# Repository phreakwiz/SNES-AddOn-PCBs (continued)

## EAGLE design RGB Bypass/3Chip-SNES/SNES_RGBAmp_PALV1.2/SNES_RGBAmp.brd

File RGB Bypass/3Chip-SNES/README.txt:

SNES_RGBAmp: for PAL 3Chip-SNES boards (SNSP-CPU-01/02)  
  
-----------------------------------------------------------------------------------  
  
Installation:  
  
  - remove R8, R9, R13, R14, R18, R19 and Q4, Q6, Q8 from the SNES mainboard  
  - solder the three 1.87kOhm resistors to R8, R13 and R18  
  - solder the three 750Ohm resistors to R9, R14 and R19  
  - solder the directly beneath the MultiAV  
  - connect pad 'R' with the pad where the base of Q4 was  
  - connect pad 'G' with the pad where the base of Q6 was  
  - connect pad 'B' with the pad where the base of Q8 was  
  
While modding some components on the PCB may vary depending on your RGB cable you want to use.  
See the notes related to the components!    
  
-----------------------------------------------------------------------------------  
  
Components needed:  
  
1. Parts for the PCB:  
 - 1x THS7314 SOIC-8 package   
  
 - 1x 22uF/6.3V tantalum capacitor type-C package  
 - 1x 100nF/50V ceramic capacitor 0805 package  
  
 - 3x 82nF/50V ceramic capacitor 0805 package  
 - 3x 3.6MOhm resistor 0805 package (0.125W, 1% tolerance should be fine)   
  
2.a) Additional parts for the PCB for using NTSC-cable schematic [1]:  
 - 3x 75Ohm resistor 0805 package (0.125W, 1% tolerance should be fine)  
  
2.b) Additional parts for using PAL-cable schematic [1]:  
 - 3x 39Ohm resistor 0805 package (0.125W, 1% tolerance should be fine) [2]  
 - 3x 330uF/6.3V tantalum capacitor type-D package  
  
2.c) Additional parts for a cable with direct wiring RGB [1]:  
 - 3x 75Ohm resistor 0805 package (0.125W, 1% tolerance should be fine)  
 - 3x 330uF/6.3V tantalum capacitor type-D package  
  
3. Parts for the SNES mainboard:  
 - 3x 750Ohm resistor 0805 package (0.125W, 1% tolerance should be fine)  
 - 3x 1.87kOhm resistor 0805 package (0.125W, 1% tolerance should be fine)   
  
-----------------------------------------------------------------------------------  
  
Notes  
  
[1]  
Just pic one (!) and do not buy all parts. If you use NTSC-cable schematic you have to short the three jumpers on the PCB.  
  
[2]  
You could also use 6x 75Ohm resistor (0805 package (0.125W, 1% tolerance should be fine)) and stack two of them on each pad pair.

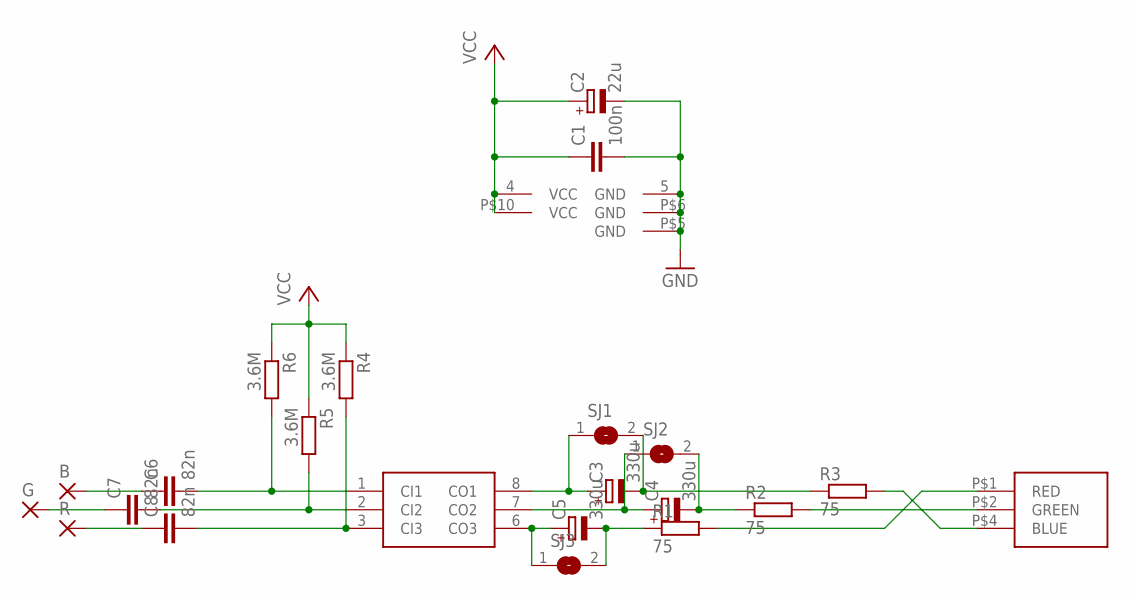
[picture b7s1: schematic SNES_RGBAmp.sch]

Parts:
B: SMD2; SMD1,27-2,54
C1: 100n; Z0805
C2: 22u; SMC_C
C3, C4, C5: 330u; SMC_D
C6, C7, C8: 82n; Z0805
G: SMD2; SMD1,27-2,54
R: SMD2; SMD1,27-2,54
R1, R2, R3: 75; Z0805
R4, R5, R6: 3.6M; Z0805
SJ1, SJ2, SJ3: SJ
U$1: THS7314
U$2: SNES_MULTIAV_RGB_ONLY

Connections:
GND: C1.2, C2.-, U$1.5 (GND), U$2.P$5 (GND), U$2.P$6 (GND)
unnamed: C6.2, R6.2, U$1.1 (CI1)
unnamed: C7.2, R5.2, U$1.2 (CI2)
unnamed: C8.2, R4.2, U$1.3 (CI3)
unnamed: C3.-, R3.1, SJ1.2
unnamed: R3.2, U$2.P$4 (BLUE)
unnamed: R2.2, U$2.P$2 (GREEN)
unnamed: C4.+, SJ2.1, U$1.7 (CO2)
unnamed: C5.-, R1.1, SJ3.2
unnamed: R1.2, U$2.P$1 (RED)
unnamed: C5.+, SJ3.1, U$1.6 (CO3)
unnamed: C3.+, SJ1.1, U$1.8 (CO1)
unnamed: C4.-, R2.1, SJ2.2
unnamed: B.1, C6.1
unnamed: C7.1, G.1
unnamed: C8.1, R.1
VCC: C1.1, C2.+, R4.1, R5.1, R6.1, U$1.4 (VCC), U$2.P$10 (VCC)

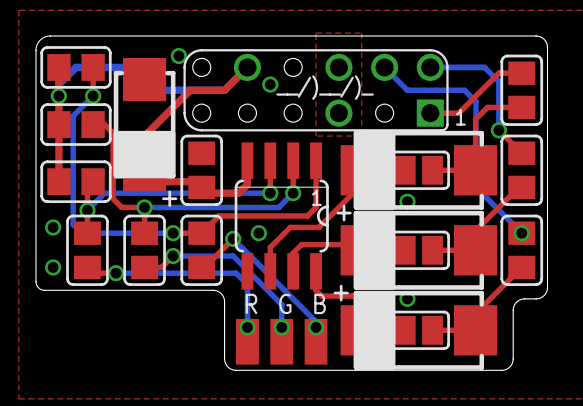
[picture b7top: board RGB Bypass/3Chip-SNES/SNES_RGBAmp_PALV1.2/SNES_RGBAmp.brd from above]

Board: 2 copper layers, 28.4 x 18.6 mm, 22 parts (0 on the bottom side), 17 nets.

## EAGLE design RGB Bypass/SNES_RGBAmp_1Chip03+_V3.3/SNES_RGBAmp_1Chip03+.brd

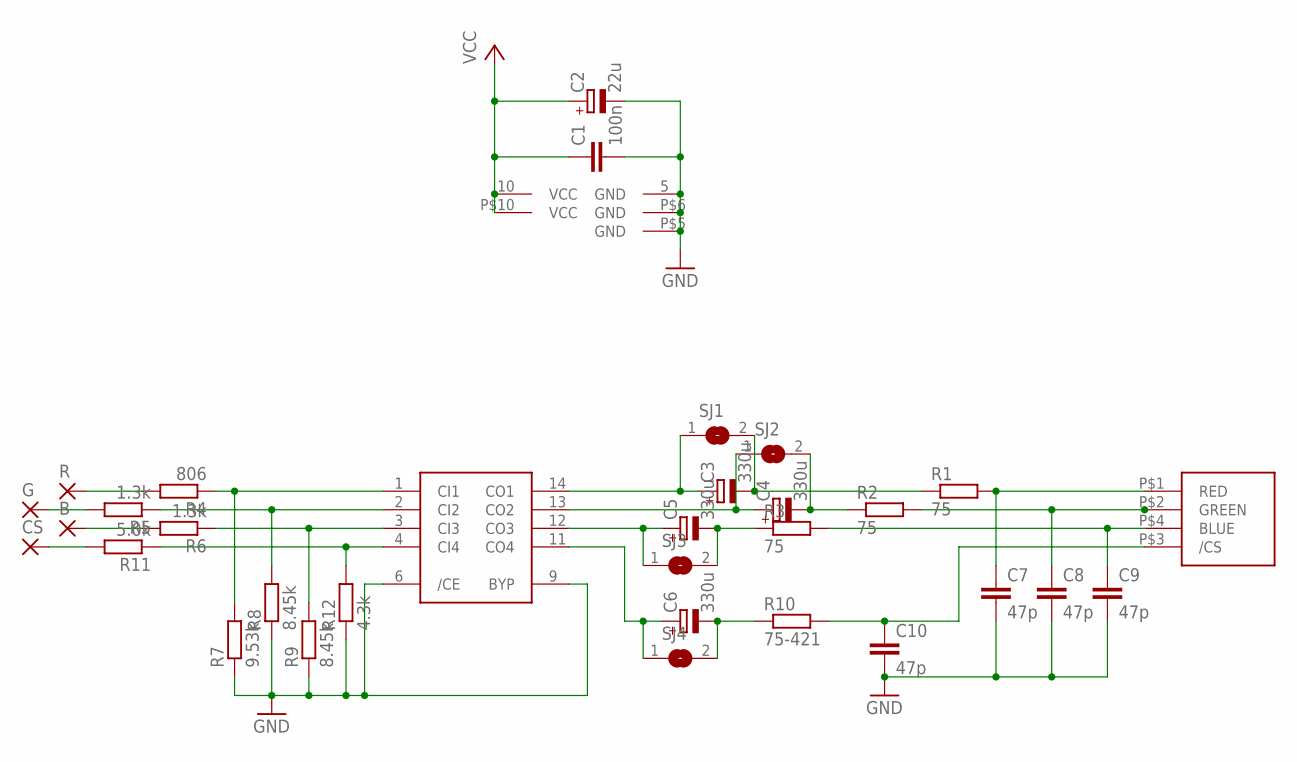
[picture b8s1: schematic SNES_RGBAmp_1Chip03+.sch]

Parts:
B: SMD2; SMD1,27-2,54
C1: 100n; Z0805
C2: 22u; SMC_C
C3, C4, C5, C6: 330u; SMC_D
C7, C8, C9, C10: 47p; Z0805
CS: SMD2; SMD1,27-2,54
G: SMD2; SMD1,27-2,54
R: SMD2; SMD1,27-2,54
R1, R2, R3: 75; Z0805
R4: 806; Z0805
R5, R6: 1.3k; Z0805
R7: 9.53k; Z0805
R8, R9: 8.45k; Z0805
R10: 75-421; Z0805
R11: 5.0k; Z0805
R12: 4.3k; Z0805
SJ1, SJ2, SJ3, SJ4: SJ
U$2: THS7374
U$3: SNES_MULTIAV_RGBC_ONLY

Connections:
GND: C1.2, C2.-, C7.2, C8.2, C9.2, C10.2, R7.1, R8.1, R9.1, R12.1, U$2.5 (GND), U$2.6 (/CE), U$2.9 (BYP), U$3.P$5 (GND), U$3.P$6 (GND)
unnamed: R4.1, R7.2, U$2.1 (CI1)
unnamed: R5.1, R8.2, U$2.2 (CI2)
unnamed: C3.-, R1.1, SJ1.2
unnamed: C7.1, R1.2, U$3.P$1 (RED)
unnamed: C8.1, R2.2, U$3.P$2 (GREEN)
unnamed: C4.+, SJ2.1, U$2.13 (CO2)
unnamed: C5.-, R3.1, SJ3.2
unnamed: C9.1, R3.2, U$3.P$4 (BLUE)
unnamed: R11.1, R12.2, U$2.4 (CI4)
unnamed: C5.+, SJ3.1, U$2.12 (CO3)
unnamed: C3.+, SJ1.1, U$2.14 (CO1)
unnamed: C4.-, R2.1, SJ2.2
unnamed: R.1, R4.2
unnamed: G.1, R5.2
unnamed: B.1, R6.2
unnamed: CS.1, R11.2
unnamed: C6.+, SJ4.1, U$2.11 (CO4)
unnamed: C6.-, R10.1, SJ4.2
unnamed: C10.1, R10.2, U$3.P$3 (/CS)
R9: R6.1, R9.2, U$2.3 (CI3)
VCC: C1.1, C2.+, U$2.10 (VCC), U$3.P$10 (VCC)

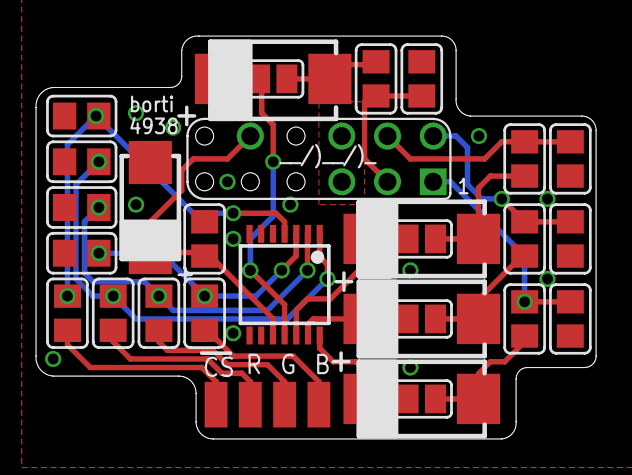
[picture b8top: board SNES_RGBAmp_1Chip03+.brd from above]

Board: 2 copper layers, 31.1 x 22.4 mm, 32 parts (0 on the bottom side), 22 nets.

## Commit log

2015-07-21 revert small typos
2015-08-06 New folder structure and improvements on the uIGR code
    Here are some notes out of my other repository:
    >>
    improved data sampling, combined code for with(out) lock option
    - data sampling on falling clock edge
    - last value taken right before the edge detection
    - support of third party controllers like micros UWRC(V2)
2015-08-07 Minor improvement I forgot about the SGB support. With the SGB specific controller reading the validity test fails if RAIF is cleared after the reading button B.
2015-08-26 Minor updates for the Logo-PCBs: - move resistors for LEDs to the LED PCB - LEDs can be either in 0805 or P-LCC-2 package
2015-09-23 Remove firmware folder and place download links instead It is easier for me to keep it up to date ;)
2015-09-25 Code Backup for ATTiny45
    - created by jensma 2012 (jensam.de)
    - ported to atmel studio by sanni 2013
    - modified by borti4938 2015
    Code runs best at 8MHz
    use code in *_on_* folder if you want the LEDs to be on after animation
    use code in *_off_* folder if you want the LEDs to be switched off after animation
2015-09-25 ready update
2015-10-15 Update Design: - minor changes and adjustments
2015-10-15 RGB Bypass Version Update: - adjustment of wires - mirrored positioning of R, G and B pad - exact values for resistors - add a version with CSYNC-buffering (for 1Chip03 boards and later) - more detai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
2015-10-16 README update
2015-10-26 Lib update: still nasty sorted and awful design (this will never change :P)
2015-11-04 correct a small error in README-file
2015-12-03 rename files
2015-12-03 Minor Updates: - Dual design for crystals (SNES-1Chip_MR_QID only); SMD and THT crystals are now supported (If THT crystals are used, SMD pads have to isolated, manually.) - minor tweaks of traces - 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
2015-12-18 Update: 330uF tantalum in CSYNC line at the output of the THS7374.
2016-02-01 Update silkscreen
2016-02-11 move R12 to avoid a slight overlapping between the PCB and a mounting screw in SNES Mini and SFC Jr.
2016-02-19 add part list for multi region boards in QID
2016-02-19 add a hint for using THT crystals
2016-02-20 update part list (fix issue #2)
2016-02-21 new folder structure
2016-02-21 introduce RGB-amp for the 3Chip-SNES (PAL models only) with a THS7314
2016-02-23 update tantal-cap sizes
2016-02-24 pictures for issue #3
2016-03-18 A user-note for the region patch
2016-04-22 update firmware text
2016-04-22 add thermals to ground pad (easier to solder) and reduce PCB size a bit
2016-04-22 add gerber files for MR QID
2016-04-22 rename folders a bit, add thermals to GND pads
2016-04-22 remove deprecated designs
2016-04-22 update design: move GND pad
2016-04-22 update libs
2016-10-18 Backup V3
2016-10-18 Initial commit V4
2016-11-07 Correct resistor values for brightness correction
2017-01-26 sd2snes to Rev.H Mod
2017-02-02 Clarify that setting HWID is an optional step
2017-02-13 go to version 4.1
2017-02-14 Change resistor values
2017-03-19 expression changed
2017-07-14 additional preparation step for Rev.G sd2snes
2017-11-17 Update README and BOM
2017-11-19 include some feedback. Thanks to shartqueefa (shmups forum user) for that :)
2017-11-20 some refinements on "brightness and ghosting issue" description
2017-11-23 clean up
2017-12-07 revert a small copy n paste error
2017-12-27 add LICENSE
2018-01-24 added missing KiCad files
2018-01-24 deleted backup files
2018-02-12 update digital audio mod incl a new no-cut design with coax
2018-02-14 PCB Update
2018-02-16 small bugfix in values (MPNs were right)
2018-02-23 SNES 1Chip replacement
2018-04-17 fix some bugs in BOM
2018-05-26 Minor typo bugfix. Thanks to Nope (twitter @Nohpuh)
2019-06-10 move classic multi-region mod
2019-06-15 update license
2019-06-16 initial commit multi region pcb with dejitter included
2019-06-17 add a header to readme
2019-06-17 general notes on installation and a common picture
2019-06-17 initial commit: SNS-CPU-RGB-01 installation
2019-06-17 typo removed
2019-06-19 rename folder of EAGLE gerber legacy format output (issue #7)
2019-06-19 some additional remarks
2019-06-19 installation guide for the PAL SNSP-CPU-1CHIP-01/02 mainboard
2019-07-23 add missing dfo gui files
2019-07-23 add missing installation step
2019-07-23 add installation guide for the SNN-CPU-01 (SNES2) mainboard
2019-08-13 add installation readme for SNSP-CPU-01 and SNSP-CPU-02 boards
2019-08-14 headline fixes
2019-08-14 Add description of C59 fix
2019-08-14 add installation guide SNS-CPU-APU-01
2019-08-14 pic update
2019-08-14 PCB update: - double /CS.i pad - color carrier generate inside CPLD (trace removed) - replace resistor arrays by simple components - add footprint for resistor from SNES mainboard to have resistor no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
2019-08-14 version typo removed
2019-10-29 clarification
2020-03-22 update PCB design: - selectable sync level for the buffered output - video buffer for sync instead of transistor
2020-03-25 update PCB design: - selectable sync level for the buffered output - video buffer for sync instead of transistor - color carrier fix applied - some GND between sub-carrier and master clock output
2020-03-30 change link from configuration file to compiled hex
